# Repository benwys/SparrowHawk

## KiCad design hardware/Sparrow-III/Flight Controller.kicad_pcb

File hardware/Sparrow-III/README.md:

# Sparrow-III

Projekt KiCad: **Flight Controller.kicad_pro**.

- [Dokumentacja i stan prac](../../docs/Sparrow-III/README.md)
- [Backlog](../../docs/Sparrow-III/BACKLOG.md)
- [Raport kontroli](../../docs/Sparrow-III/REVIEW.md)
- [Skrypty](../../tools/Sparrow-III/README.md)

Biblioteki są lokalne w `Libraries/`; tabele używają `${KIPRJMOD}`.
Etap: placement, przed pełnym routingiem.

[Wspólna próba trasowania](attempts/placement-closure-20260912/Flight%20Controller.kicad_pro) jest osobnym projektem z miedzią. Główny placement pozostaje bez routingu.

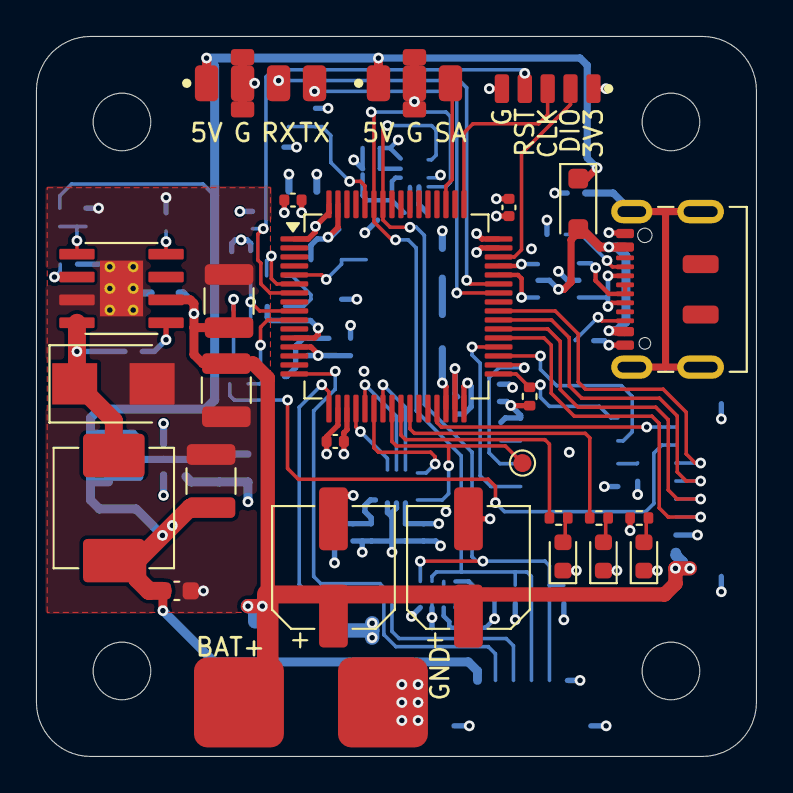
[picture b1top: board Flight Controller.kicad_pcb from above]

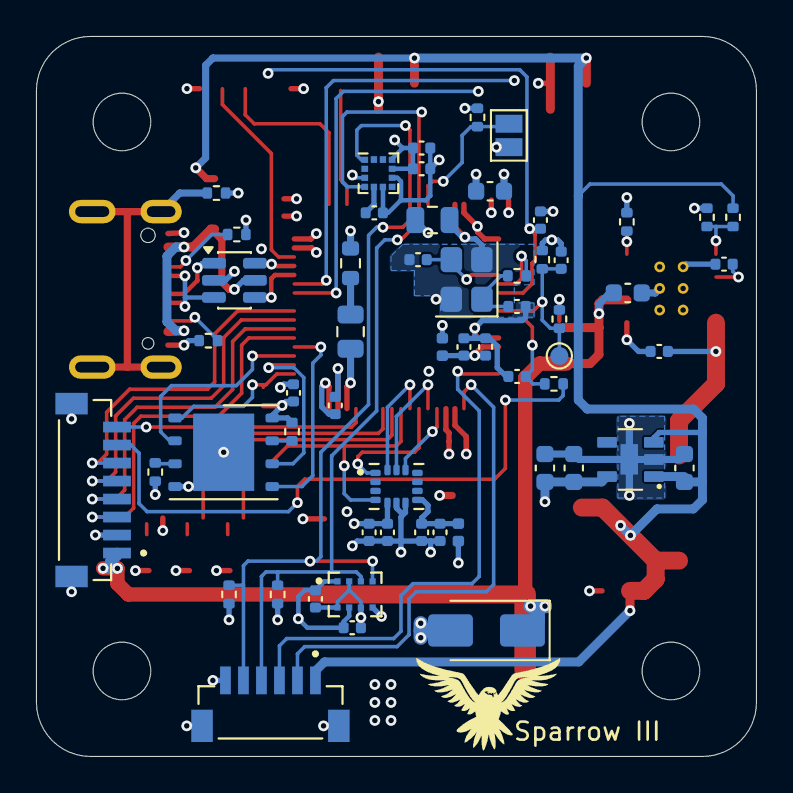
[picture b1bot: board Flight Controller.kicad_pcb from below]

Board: 4 copper layers, 40.0 x 40.0 mm, 89 parts (58 on the bottom side), 60 nets.

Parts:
C_3V3_BULK1, C_5V_BULK1: 10uF; C_0603_1608Metric
C_B1, C_B5: 47uF; CP_Elec_6.3x5.8
C_BARO1, C_BARO2: 100nF; C_0402_1005Metric
C_BUCK_BOOT1: 100nF; C_0402_1005Metric
C_BUCK_IN1, C_BUCK_IN2: 4.7uF; C_1210_3225Metric
C_BUCK_IN3: 100nF; C_0603_1608Metric
C_BUCK_OUT1: 100uF; C_1210_3225Metric
C_BUCK_SS1: 22nF; C_0402_1005Metric
C_CURR_F1: 1uF; C_0402_1005Metric
C_FLASH1: 100nF; C_0402_1005Metric
C_HSE1, C_HSE2: 12pF; C_0402_1005Metric
C_IMU_VDD1: 2.2uF; C_0402_1005Metric
C_IMU_VDD2: 100nF; C_0402_1005Metric
C_IMU_VIO1: 100nF; C_0402_1005Metric
C_IMU_VIO2: 10nF; C_0402_1005Metric
C_LDO_IN1: 2.2uF; C_0603_1608Metric
C_LDO_OUT1: 2.2uF; C_0603_1608Metric
C_MAG_BULK1: 22uF; C_0805_2012Metric
C_MAG_SET1: 220nF; C_0402_1005Metric
C_MAG_VDD1: 100nF; C_0402_1005Metric
C_MAG_VIO1: 100nF; C_0402_1005Metric
C_NRST1: 100nF; C_0402_1005Metric
C_VBAT_ADC1: 100nF; C_0402_1005Metric
C_VCAP1: 4.7uF; C_0805_2012Metric
C_VDD1, C_VDD2, C_VDD3, C_VDD4: 100nF; C_0402_1005Metric
C_VDDA1: 1uF; C_0402_1005Metric
C_VDDA_HF1: 100nF; C_0402_1005Metric
C_VDD_BULK1: 4.7uF; C_0603_1608Metric
D_BUCK1: STPS3H100U; D_SMB
D_TVS1: SMAJ26A; D_SMA
D_USB_VBUS1: PMEG2010AEH; D_SOD-123F
FB_IMU1: 600R @ 100MHz; L_0402_1005Metric
FB_VDDA1: 100R @ 100MHz; L_0402_1005Metric
H_MNT1, H_MNT2, H_MNT3, H_MNT4: MountingHole 3.2mm_M3; MountingHole_3.2mm_M3
JP_BOOT0: Jumper2; SolderJumper-2_P1.3mm_Open_Pad1.0x1.5mm
J_BAT1: Conn_01x02; VBAT_SolderPad_2x_5x5mm
J_ESC1: BM08B-SRSS-TB_LF__SN_; JST_BM08B-SRSS-TB_LF__SN_
J_GPS1: BM06B-SRSS-TB_LF__SN_; JST_BM06B-SRSS-TB_LF__SN_
J_RX1: RX Pads; SolderPads_RX_1x04
J_SWD1: SWD Pads; SolderPads_SWD_1x05
J_USB1: DX07S016JA1R1500; USB_C_Receptacle_JAE_DX07S016JA1R1500
J_VTX2: VTX: 5V / GND / SA; SolderPads_VTX_1x03
LED_PWR1: LED Green 0603; LED_0603_1608Metric
LED_STAT1: LED Blue 0603; LED_0603_1608Metric
LED_STAT2: LED Red 0603; LED_0603_1608Metric
LOGO1: Sparrowhawk_Logo
L_BUCK1: 6.8uH; L_Vishay_IHLP-2525CZ-01
R_BOOT0: 10k; R_0402_1005Metric
R_BUCK_FB1: 100k; R_0402_1005Metric
R_BUCK_FB2: 17.8k; R_0402_1005Metric
R_BUCK_RT1: 49.9k; R_0402_1005Metric
R_CC1, R_CC2: 5.1k; R_0402_1005Metric
R_CURR_F1: 1k; R_0402_1005Metric
R_FLASH_CS1: 10k; R_0402_1005Metric
R_FLASH_HD1: 10k; R_0402_1005Metric
R_FLASH_WP1: 10k; R_0402_1005Metric
R_HSE2: 0R; R_0402_1005Metric
R_I2C_SCL1, R_I2C_SDA1: 4.7k; R_0402_1005Metric
R_LED1, R_LED2, R_LED3: 1k; R_0402_1005Metric
R_USB_SH1: 0R; R_0402_1005Metric
R_VBAT_D1: 100k; R_0402_1005Metric
R_VBAT_D2: 10k; R_0402_1005Metric
R_VCAP_ESR1: 0.15R; R_0603_1608Metric
TP_IMU_INT_0: Test Point; TestPoint_Pad_D1.0mm
TP_VBAT_ADC_0: Test Point; TestPoint_Pad_D1.0mm
U_BARO1: DPS368; XDCR_DPS310
U_BUCK1: LMR14030SDDAR; SOIC127P600X170-9N_SparrowIII
U_ESD1: USBLC6-2SC6; SOT-23-6
U_FLASH1: W25Q128JVPIQ; WSON-8-1EP_6x5mm_P1.27mm_EP3.4x4.3mm
U_IMU1: ICM-42688-P; PQFN50P300X250X97-14N
U_LDO1: TLV75533PDYDR; SOT-23-5_ThermalPad_TI_DYD0005A
U_MAG1: LIS2MDLTR; LGA-12_2x2mm_P0.5mm
U_MCU1: STM32F722RETx; LQFP-64_10x10mm_P0.5mm
Y_HSE1: 8MHz; Crystal_SMD_3225-4Pin_3.2x2.5mm

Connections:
+3V3: C_3V3_BULK1.1, C_BARO1.1, C_BARO2.1, C_FLASH1.1, C_IMU_VIO1.1, C_IMU_VIO2.1, C_LDO_OUT1.1, C_MAG_BULK1.1, C_MAG_VDD1.1, C_MAG_VIO1.1, C_VDD1.1, C_VDD2.1, C_VDD3.1, C_VDD4.1, C_VDD_BULK1.1, FB_IMU1.2, FB_VDDA1.1, JP_BOOT0.1 (A), J_SWD1.1, R_FLASH_CS1.1, R_FLASH_HD1.1, R_FLASH_WP1.1, R_I2C_SCL1.1, R_I2C_SDA1.2, R_LED1.1, U_BARO1.2 (~CSB), U_BARO1.6 (VDDIO), U_BARO1.8 (VDD), U_FLASH1.8 (VCC), U_IMU1.5 (VDDIO), U_LDO1.5 (VOUT), U_MAG1.3 (~CS), U_MAG1.9 (Vdd), U_MAG1.10 (Vdd_IO), U_MCU1.1 (VBAT), U_MCU1.19 (VDD), U_MCU1.32 (VDD), U_MCU1.48 (VDD), U_MCU1.64 (VDD)
+5V: C_5V_BULK1.1, C_BUCK_OUT1.1, C_LDO_IN1.1, D_USB_VBUS1.1 (K), J_GPS1.1, J_RX1.1, J_VTX2.1, L_BUCK1.2, R_BUCK_FB1.1, U_LDO1.1 (VIN), U_LDO1.3 (EN)
/Interfaces&IO/+5V_USB: D_USB_VBUS1.2 (A), J_USB1.A4 (VBUS), J_USB1.A9 (VBUS), J_USB1.B4 (VBUS), J_USB1.B9 (VBUS), U_ESD1.5 (VBUS)
/Interfaces&IO/ESC_CURR: C_CURR_F1.1, R_CURR_F1.1, U_MCU1.10 (PC2)
/Interfaces&IO/ESC_CURR_IN: J_ESC1.7, R_CURR_F1.2
/Interfaces&IO/ESC_TEL: J_ESC1.8, U_MCU1.29 (PB11)
/Interfaces&IO/GPS_RX: J_GPS1.2, U_MCU1.17 (PA3)
/Interfaces&IO/GPS_TX: J_GPS1.3, U_MCU1.16 (PA2)
/Interfaces&IO/M1: J_ESC1.3, U_MCU1.37 (PC6)
/Interfaces&IO/M2: J_ESC1.4, U_MCU1.38 (PC7)
/Interfaces&IO/M3: J_ESC1.5, U_MCU1.39 (PC8)
/Interfaces&IO/M4: J_ESC1.6, U_MCU1.40 (PC9)
/Interfaces&IO/RC_RX: J_RX1.3, U_MCU1.43 (PA10)
/Interfaces&IO/RC_TX: J_RX1.4, U_MCU1.42 (PA9)
/Interfaces&IO/USB_C_DN: J_USB1.A7 (D-), J_USB1.B7 (D-), U_ESD1.3 (I/O2)
/Interfaces&IO/USB_C_DP: J_USB1.A6 (D+), J_USB1.B6 (D+), U_ESD1.1 (I/O1)
/Interfaces&IO/USB_DN: U_ESD1.4 (I/O2), U_MCU1.44 (PA11)
/Interfaces&IO/USB_DP: U_ESD1.6 (I/O1), U_MCU1.45 (PA12)
/Interfaces&IO/VTX_TX: J_VTX2.3, U_MCU1.51 (PC10)
/MCU Core/FLASH_CS: R_FLASH_CS1.2, U_FLASH1.1 (~CS), U_MCU1.33 (PB12)
/MCU Core/I2C1_SCL: J_GPS1.5, R_I2C_SCL1.2, U_BARO1.4 (SCK), U_MAG1.1 (SCL/SPC), U_MCU1.58 (PB6)
/MCU Core/I2C1_SDA: J_GPS1.4, R_I2C_SDA1.1, U_BARO1.3 (SDI), U_MAG1.4 (SDA/SDI/SDO), U_MCU1.59 (PB7)
/MCU Core/IMU_CS: U_IMU1.12 (AP_CS), U_MCU1.20 (PA4)
/MCU Core/IMU_INT: TP_IMU_INT_0.1 (1_1), U_IMU1.4 (INT1/INT), U_MCU1.24 (PC4)
/MCU Core/LED_STAT1: R_LED2.1, U_MCU1.25 (PB0)
/MCU Core/LED_STAT2: R_LED3.1, U_MCU1.26 (PB1)
/MCU Core/NRST: C_NRST1.1, J_SWD1.4, U_MCU1.7 (NRST)
/MCU Core/RCC_OSC_IN: C_HSE2.2, U_MCU1.5 (PH0), Y_HSE1.3
/MCU Core/RCC_OSC_OUT: R_HSE2.2, U_MCU1.6 (PH1)
/MCU Core/SPI1_MISO: U_IMU1.1 (AP_SDO/AP_AD0), U_MCU1.22 (PA6)
/MCU Core/SPI1_MOSI: U_IMU1.14 (AP_SDA/AP_SDIO/AP_SDI), U_MCU1.23 (PA7)
/MCU Core/SPI1_SCK: U_IMU1.13 (AP_SCL/AP_SCLK), U_MCU1.21 (PA5)
/MCU Core/SPI2_MISO: U_FLASH1.2 (DO/IO_{1}), U_MCU1.35 (PB14)
/MCU Core/SPI2_MOSI: U_FLASH1.5 (DI/IO_{0}), U_MCU1.36 (PB15)
/MCU Core/SPI2_SCK: U_FLASH1.6 (CLK), U_MCU1.34 (PB13)
/MCU Core/SWCLK: J_SWD1.3, U_MCU1.49 (PA14)
/MCU Core/SWDIO: J_SWD1.2, U_MCU1.46 (PA13)
/MCU Core/VBAT_ADC: C_VBAT_ADC1.1, R_VBAT_D1.1, R_VBAT_D2.2, TP_VBAT_ADC_0.1 (1_1), U_MCU1.9 (PC1)
/MCU Core/VCAP_RETURN: C_VCAP1.2, R_VCAP_ESR1.1
/Sensors/MAG_C1: C_MAG_SET1.1, U_MAG1.5 (C1)
GND: C_3V3_BULK1.2, C_5V_BULK1.2, C_B1.2, C_B5.2, C_BARO1.2, C_BARO2.2, C_BUCK_IN1.2, C_BUCK_IN2.2, C_BUCK_IN3.2, C_BUCK_OUT1.2, C_BUCK_SS1.2, C_CURR_F1.2, C_FLASH1.2, C_HSE1.1, C_HSE2.1, C_IMU_VDD1.2, C_IMU_VDD2.2, C_IMU_VIO1.2, C_IMU_VIO2.2, C_LDO_IN1.2, C_LDO_OUT1.2, C_MAG_BULK1.2, C_MAG_SET1.2, C_MAG_VDD1.2, C_MAG_VIO1.2, C_NRST1.2, C_VBAT_ADC1.2, C_VDD1.2, C_VDD2.2, C_VDD3.2, C_VDD4.2, C_VDDA1.2, C_VDDA_HF1.2, C_VDD_BULK1.2, D_BUCK1.2 (A), D_TVS1.2 (A2), J_BAT1.2, J_ESC1.2, J_ESC1.S1 (SHIELD), J_ESC1.S2 (SHIELD), J_GPS1.6, J_GPS1.S1 (SHIELD), J_GPS1.S2 (SHIELD), J_RX1.2, J_RX1.S1 (SHIELD), J_RX1.S2 (SHIELD), J_SWD1.5, J_USB1.A1 (GND), J_USB1.A12 (GND), J_USB1.B1 (GND), J_USB1.B12 (GND), J_VTX2.2, LED_PWR1.1 (K), LED_STAT1.1 (K), LED_STAT2.1 (K), R_BOOT0.1, R_BUCK_FB2.2, R_BUCK_RT1.2, R_CC1.2, R_CC2.2, R_USB_SH1.2, R_VBAT_D2.1, R_VCAP_ESR1.2, U_BARO1.1 (GND), U_BARO1.5 (SDO), U_BARO1.7 (GND), U_BUCK1.7 (GND), U_BUCK1.9 (GND), U_BUCK1.V1 (GND), U_BUCK1.V2 (GND), U_BUCK1.V3 (GND), U_BUCK1.V4 (GND), U_BUCK1.V5 (GND), U_BUCK1.V6 (GND), U_ESD1.2 (GND), U_FLASH1.4 (GND), U_FLASH1.9 (EP), U_IMU1.6 (GND), U_IMU1.7 (RESV_7), U_LDO1.2 (GND), U_LDO1.6 (EP), U_MAG1.6 (GND), U_MAG1.8 (GND), U_MCU1.12 (VSSA), U_MCU1.18 (VSS), U_MCU1.31 (VSS), U_MCU1.47 (VSS), U_MCU1.63 (VSS), Y_HSE1.2 (G), Y_HSE1.4 (G)
unnamed: C_HSE1.2, R_HSE2.1, Y_HSE1.1
unnamed: C_BUCK_BOOT1.2, D_BUCK1.1 (K), L_BUCK1.1, U_BUCK1.8 (SW)
unnamed: JP_BOOT0.2 (B), R_BOOT0.2, U_MCU1.60 (BOOT0)
unnamed: J_USB1.A5 (CC1), R_CC1.1
unnamed: J_USB1.B5 (CC2), R_CC2.1
unnamed: J_USB1.SH (SHIELD), R_USB_SH1.1
unnamed: LED_PWR1.2 (A), R_LED1.2
unnamed: LED_STAT1.2 (A), R_LED2.2
unnamed: LED_STAT2.2 (A), R_LED3.2
unnamed: C_BUCK_BOOT1.1, U_BUCK1.1 (BOOT)
unnamed: R_BUCK_FB1.2, R_BUCK_FB2.1, U_BUCK1.5 (FB)
unnamed: R_BUCK_RT1.1, U_BUCK1.4 (RT/SYNC)
unnamed: C_BUCK_SS1.1, U_BUCK1.6 (SS)
unnamed: R_FLASH_HD1.2, U_FLASH1.7 (~HOLD/~RESET/IO_{3})
unnamed: R_FLASH_WP1.2, U_FLASH1.3 (~WP/IO_{2})
unnamed: C_IMU_VDD1.1, C_IMU_VDD2.1, FB_IMU1.1, U_IMU1.8 (VDD)
unnamed: C_VCAP1.1, U_MCU1.30 (VCAP_1)
unnamed: C_VDDA1.1, C_VDDA_HF1.1, FB_VDDA1.2, U_MCU1.13 (VDDA)
VBAT: C_B1.1, C_B5.1, C_BUCK_IN1.1, C_BUCK_IN2.1, C_BUCK_IN3.1, D_TVS1.1 (A1), J_BAT1.1, J_ESC1.1, R_VBAT_D1.2, U_BUCK1.2 (VIN)

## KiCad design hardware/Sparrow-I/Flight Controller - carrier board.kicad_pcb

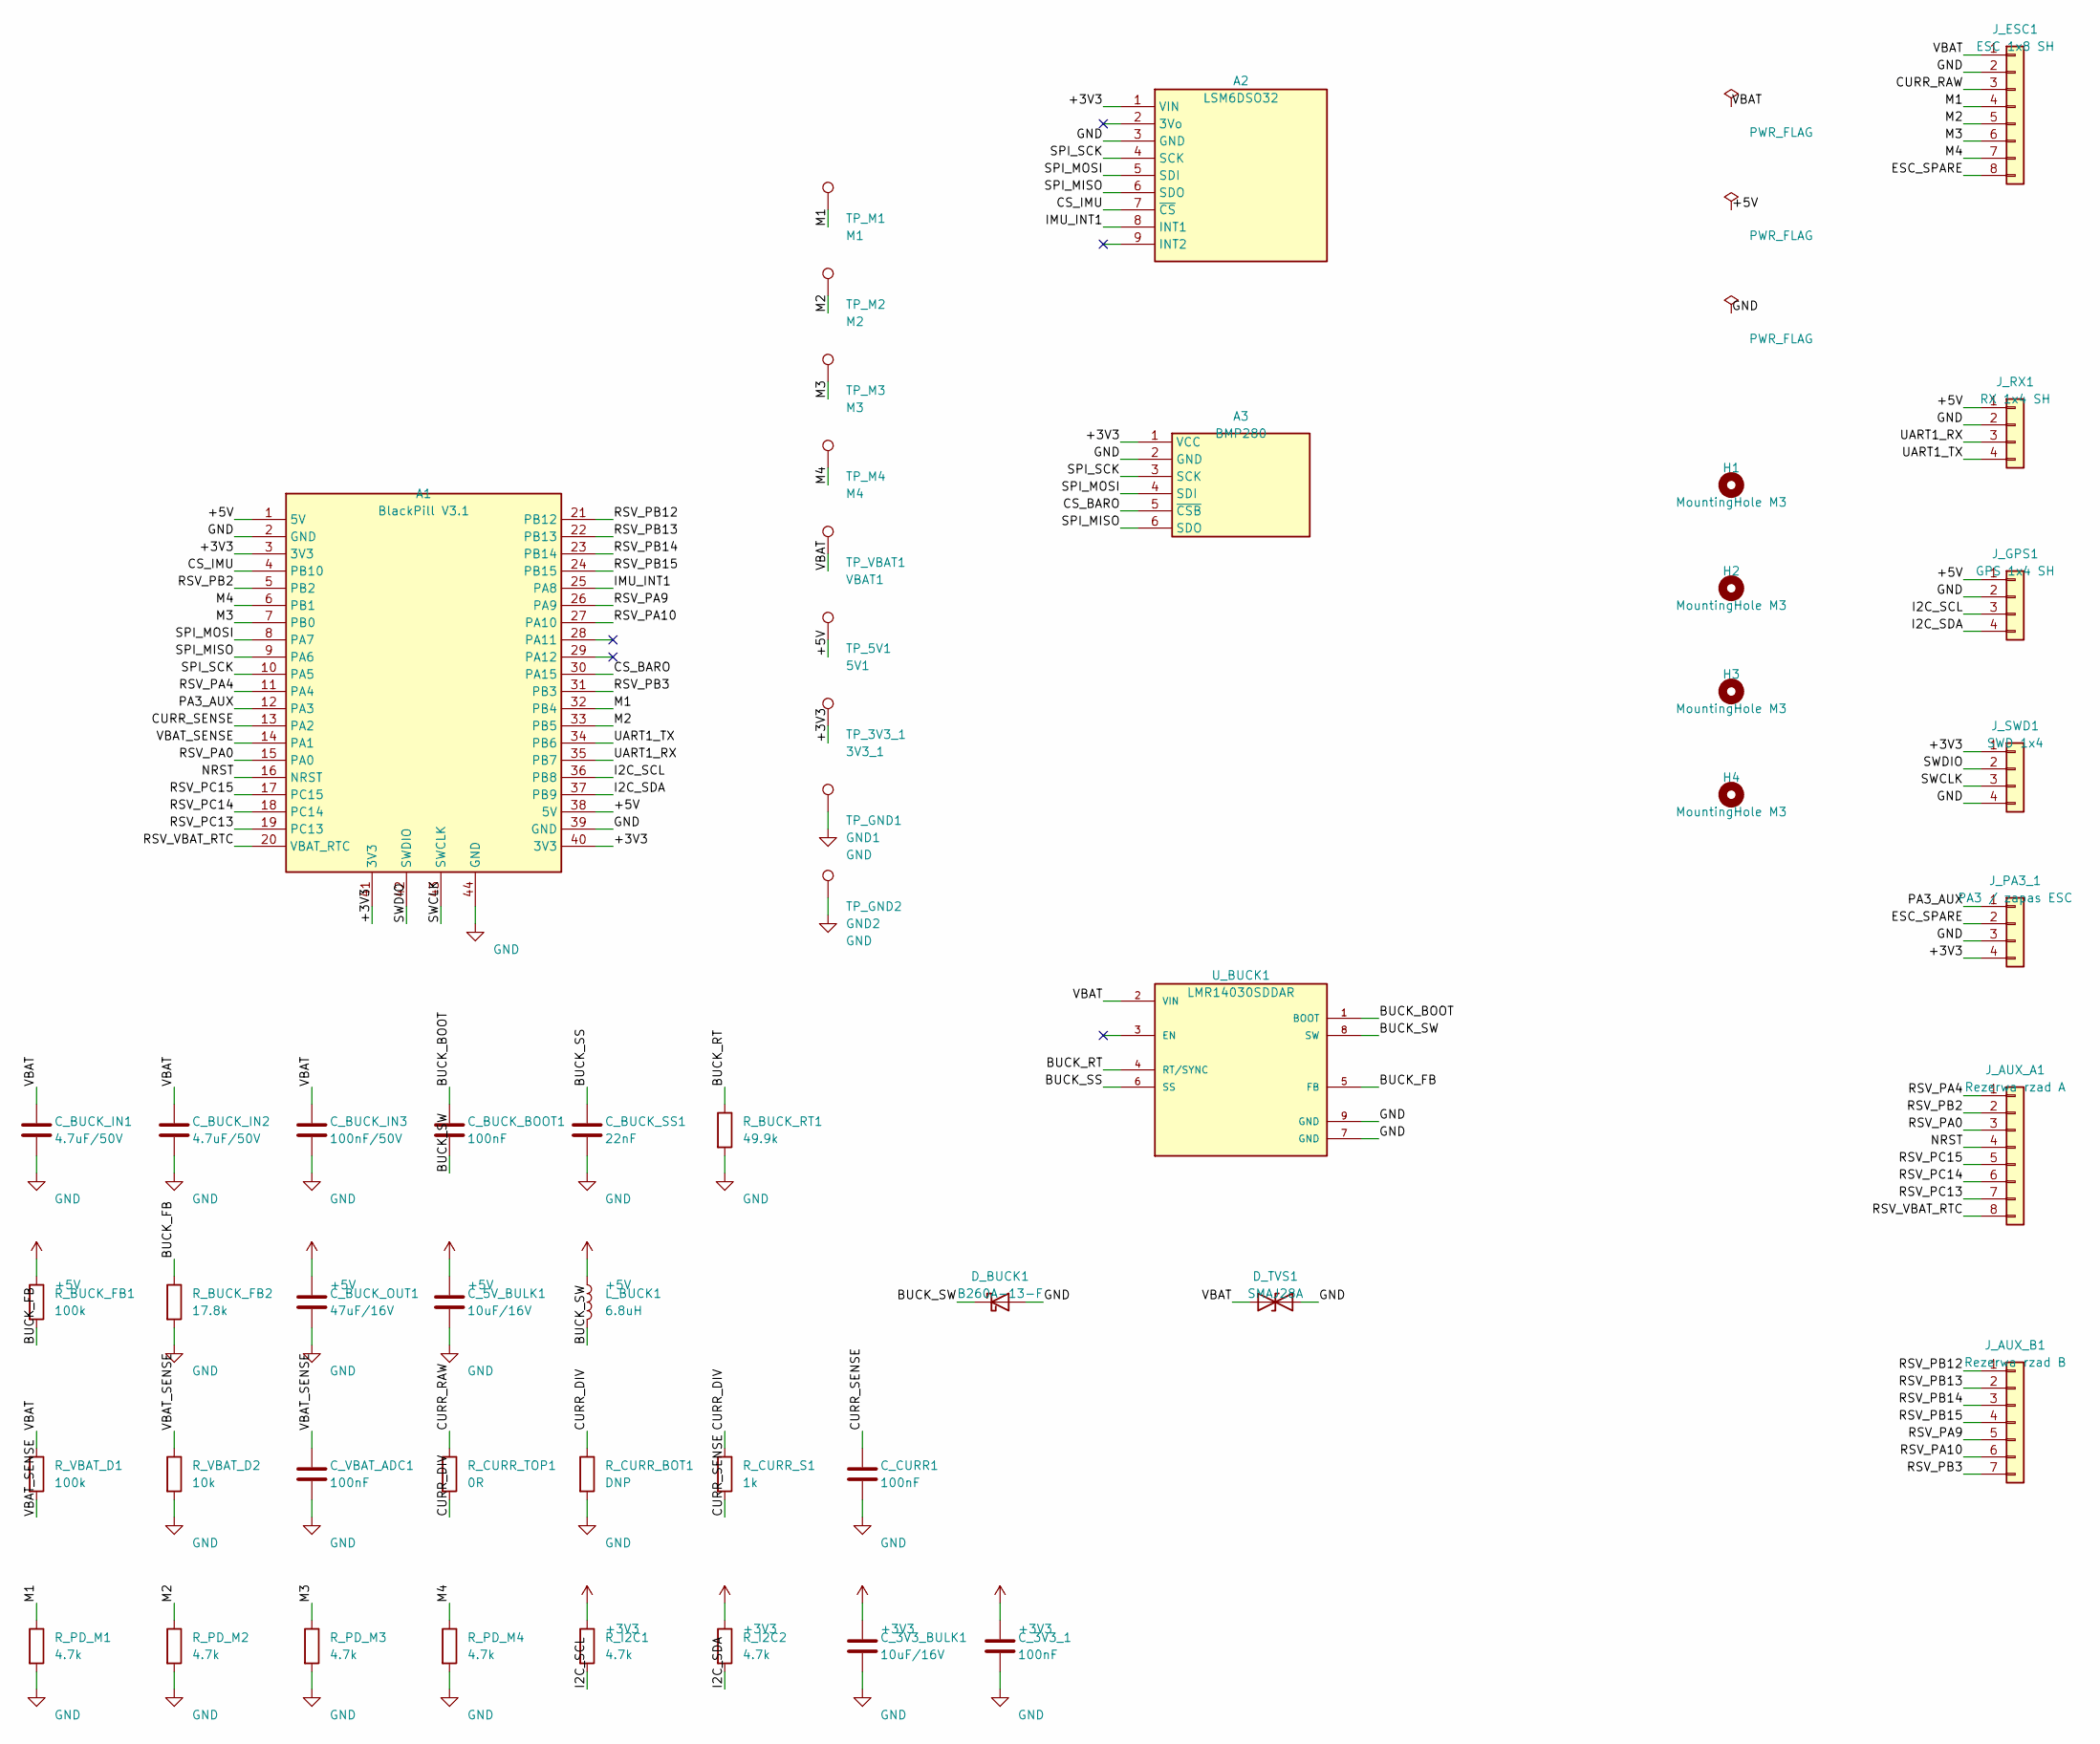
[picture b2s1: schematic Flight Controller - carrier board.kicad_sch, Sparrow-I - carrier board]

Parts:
A1: BlackPill V3.1; Module_BlackPill_STM32F411_WeAct_V31
A2: LSM6DSO32; Module_LSM6DSO32_Adafruit_4692
A3: BMP280; Module_BMP280_6pin
C_3V3_1: 100nF; C_0402_1005Metric
C_3V3_BULK1, C_5V_BULK1: 10uF/16V; C_0805_2012Metric
C_BUCK_BOOT1: 100nF; C_0402_1005Metric
C_BUCK_IN1, C_BUCK_IN2: 4.7uF/50V; C_1210_3225Metric
C_BUCK_IN3: 100nF/50V; C_0402_1005Metric
C_BUCK_OUT1: 47uF/16V; C_1210_3225Metric
C_BUCK_SS1: 22nF; C_0402_1005Metric
C_CURR1: 100nF; C_0402_1005Metric
C_VBAT_ADC1: 100nF; C_0402_1005Metric
D_BUCK1: B260A-13-F; D_SMA
D_TVS1: SMAJ28A; D_SMA
H1, H2, H3, H4: MountingHole M3; MountingHole_3.2mm_M3
J_AUX_A1: Rezerwa rzad A; PinHeader_1x08_P2.54mm_Vertical
J_AUX_B1: Rezerwa rzad B; PinHeader_1x07_P2.54mm_Vertical
J_ESC1: ESC 1x8 SH; JST_SH_SM08B-SRSS-TB_1x08-1MP_P1.00mm_Horizontal
J_GPS1: GPS 1x4 SH; JST_SH_SM04B-SRSS-TB_1x04-1MP_P1.00mm_Horizontal
J_PA3_1: PA3 / zapas ESC; PinHeader_1x04_P2.54mm_Vertical
J_RX1: RX 1x4 SH; JST_SH_SM04B-SRSS-TB_1x04-1MP_P1.00mm_Horizontal
J_SWD1: SWD 1x4; PinHeader_1x04_P2.54mm_Vertical
L_BUCK1: 6.8uH; L_Sunlord_SWPA6028S
R_BUCK_FB1: 100k; R_0402_1005Metric
R_BUCK_FB2: 17.8k; R_0402_1005Metric
R_BUCK_RT1: 49.9k; R_0402_1005Metric
R_CURR_BOT1: DNP; R_0402_1005Metric
R_CURR_S1: 1k; R_0402_1005Metric
R_CURR_TOP1: 0R; R_0402_1005Metric
R_I2C1, R_I2C2: 4.7k; R_0402_1005Metric
R_PD_M1, R_PD_M2, R_PD_M3, R_PD_M4: 4.7k; R_0402_1005Metric
R_VBAT_D1: 100k; R_0402_1005Metric
R_VBAT_D2: 10k; R_0402_1005Metric
TP_3V3_1: 3V3_1; TestPoint_Pad_D1.5mm
TP_5V1: 5V1; TestPoint_Pad_D1.5mm
TP_GND1: GND1; TestPoint_Pad_D1.5mm
TP_GND2: GND2; TestPoint_Pad_D1.5mm
TP_M1: M1; TestPoint_Pad_D1.5mm
TP_M2: M2; TestPoint_Pad_D1.5mm
TP_M3: M3; TestPoint_Pad_D1.5mm
TP_M4: M4; TestPoint_Pad_D1.5mm
TP_VBAT1: VBAT1; TestPoint_Pad_D1.5mm
U_BUCK1: LMR14030SDDAR; SOIC127P600X170-9N

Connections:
+3V3: A1.3 (3V3), A1.40 (3V3), A1.41 (3V3), A2.1 (VIN), A3.1 (VCC), C_3V3_1.1, C_3V3_BULK1.1, J_PA3_1.4, J_SWD1.1, R_I2C1.1, R_I2C2.1, TP_3V3_1.1 (1_1)
+5V: A1.1 (5V), A1.38 (5V), C_5V_BULK1.1, C_BUCK_OUT1.1, J_GPS1.1, J_RX1.1, L_BUCK1.1, R_BUCK_FB1.1, TP_5V1.1 (1_1)
/BUCK_BOOT: C_BUCK_BOOT1.1, U_BUCK1.1 (BOOT)
/BUCK_FB: R_BUCK_FB1.2, R_BUCK_FB2.1, U_BUCK1.5 (FB)
/BUCK_RT: R_BUCK_RT1.1, U_BUCK1.4 (RT/SYNC)
/BUCK_SS: C_BUCK_SS1.1, U_BUCK1.6 (SS)
/BUCK_SW: C_BUCK_BOOT1.2, D_BUCK1.1 (K), L_BUCK1.2, U_BUCK1.8 (SW)
/CS_BARO: A1.30 (PA15), A3.5 (~CSB)
/CS_IMU: A1.4 (PB10), A2.7 (~CS)
/CURR_DIV: R_CURR_BOT1.1, R_CURR_S1.1, R_CURR_TOP1.2
/CURR_RAW: J_ESC1.3, R_CURR_TOP1.1
/CURR_SENSE: A1.13 (PA2), C_CURR1.1, R_CURR_S1.2
/ESC_SPARE: J_ESC1.8, J_PA3_1.2
/I2C_SCL: A1.36 (PB8), J_GPS1.3, R_I2C1.2
/I2C_SDA: A1.37 (PB9), J_GPS1.4, R_I2C2.2
/IMU_INT1: A1.25 (PA8), A2.8 (INT1)
/M1: A1.32 (PB4), J_ESC1.4, R_PD_M1.1, TP_M1.1 (1_1)
/M2: A1.33 (PB5), J_ESC1.5, R_PD_M2.1, TP_M2.1 (1_1)
/M3: A1.7 (PB0), J_ESC1.6, R_PD_M3.1, TP_M3.1 (1_1)
/M4: A1.6 (PB1), J_ESC1.7, R_PD_M4.1, TP_M4.1 (1_1)
/NRST: A1.16 (NRST), J_AUX_A1.4
/PA3_AUX: A1.12 (PA3), J_PA3_1.1
/RSV_PA0: A1.15 (PA0), J_AUX_A1.3
/RSV_PA4: A1.11 (PA4), J_AUX_A1.1
/RSV_PA9: A1.26 (PA9), J_AUX_B1.5
/RSV_PA10: A1.27 (PA10), J_AUX_B1.6
/RSV_PB2: A1.5 (PB2), J_AUX_A1.2
/RSV_PB3: A1.31 (PB3), J_AUX_B1.7
/RSV_PB12: A1.21 (PB12), J_AUX_B1.1
/RSV_PB13: A1.22 (PB13), J_AUX_B1.2
/RSV_PB14: A1.23 (PB14), J_AUX_B1.3
/RSV_PB15: A1.24 (PB15), J_AUX_B1.4
/RSV_PC13: A1.19 (PC13), J_AUX_A1.7
/RSV_PC14: A1.18 (PC14), J_AUX_A1.6
/RSV_PC15: A1.17 (PC15), J_AUX_A1.5
/RSV_VBAT_RTC: A1.20 (VBAT_RTC), J_AUX_A1.8
/SPI_MISO: A1.9 (PA6), A2.6 (SDO), A3.6 (SDO)
/SPI_MOSI: A1.8 (PA7), A2.5 (SDI), A3.4 (SDI)
/SPI_SCK: A1.10 (PA5), A2.4 (SCK), A3.3 (SCK)
/SWCLK: A1.43 (SWCLK), J_SWD1.3
/SWDIO: A1.42 (SWDIO), J_SWD1.2
/UART1_RX: A1.35 (PB7), J_RX1.3
/UART1_TX: A1.34 (PB6), J_RX1.4
/VBAT: C_BUCK_IN1.1, C_BUCK_IN2.1, C_BUCK_IN3.1, D_TVS1.1 (A1), J_ESC1.1, R_VBAT_D1.1, TP_VBAT1.1 (1_1), U_BUCK1.2 (VIN)
/VBAT_SENSE: A1.14 (PA1), C_VBAT_ADC1.1, R_VBAT_D1.2, R_VBAT_D2.1
GND: A1.2 (GND), A1.39 (GND), A1.44 (GND), A2.3 (GND), A3.2 (GND), C_3V3_1.2, C_3V3_BULK1.2, C_5V_BULK1.2, C_BUCK_IN1.2, C_BUCK_IN2.2, C_BUCK_IN3.2, C_BUCK_OUT1.2, C_BUCK_SS1.2, C_CURR1.2, C_VBAT_ADC1.2, D_BUCK1.2 (A), D_TVS1.2 (A2), J_ESC1.2, J_GPS1.2, J_PA3_1.3, J_RX1.2, J_SWD1.4, R_BUCK_FB2.2, R_BUCK_RT1.2, R_CURR_BOT1.2, R_PD_M1.2, R_PD_M2.2, R_PD_M3.2, R_PD_M4.2, R_VBAT_D2.2, TP_GND1.1 (1_1), TP_GND2.1 (1_1), U_BUCK1.7 (GND), U_BUCK1.9 (GND), U_BUCK1.V1 (GND), U_BUCK1.V2 (GND), U_BUCK1.V3 (GND), U_BUCK1.V4 (GND), U_BUCK1.V5 (GND), U_BUCK1.V6 (GND)

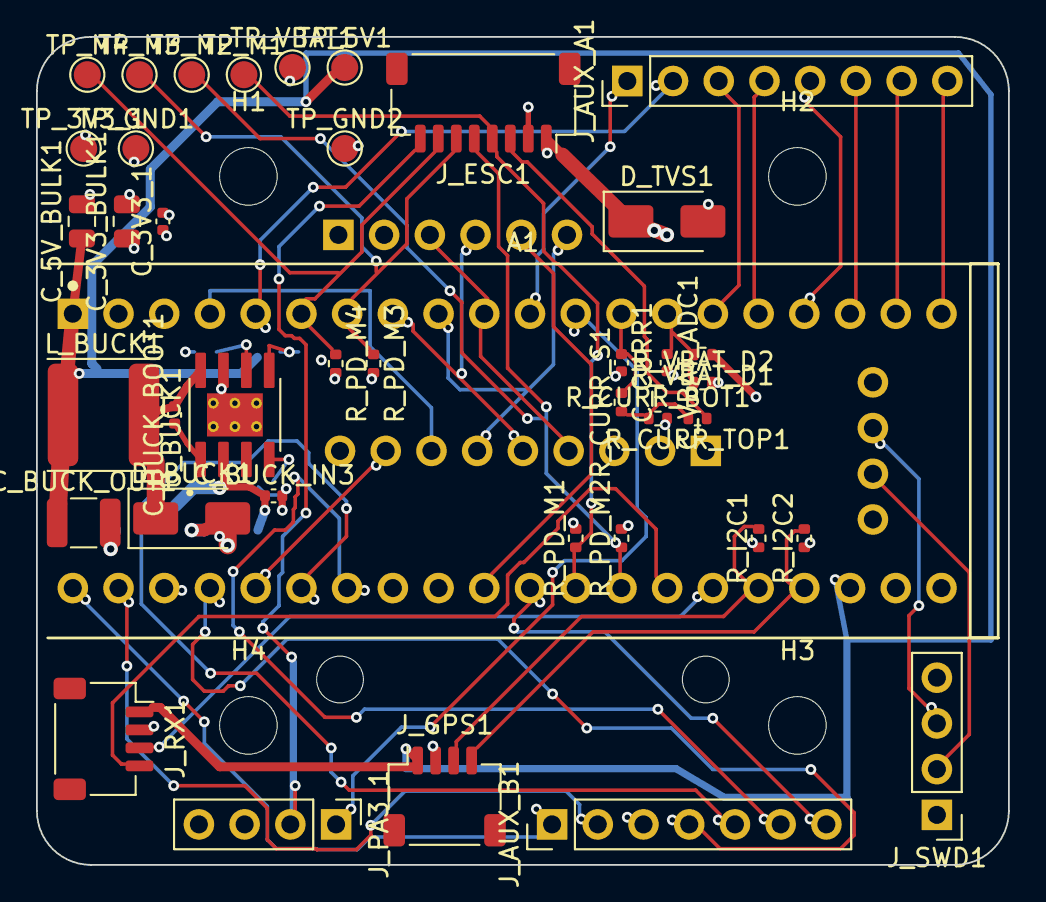
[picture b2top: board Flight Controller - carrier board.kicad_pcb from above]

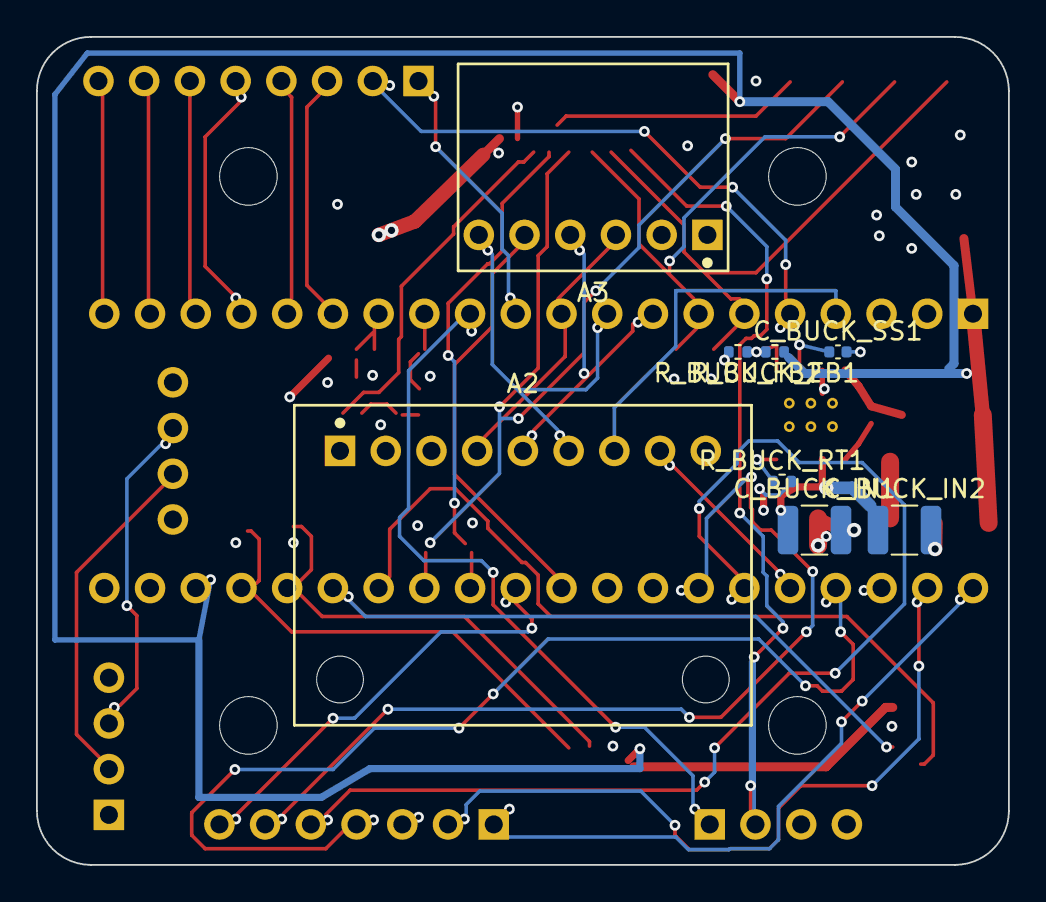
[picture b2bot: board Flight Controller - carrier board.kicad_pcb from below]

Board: 4 copper layers, 54.0 x 46.0 mm, 52 parts (8 on the bottom side), 46 nets.

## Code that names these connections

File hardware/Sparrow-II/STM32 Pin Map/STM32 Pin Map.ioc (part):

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Mcu.Name=STM32F722R(C-E)Tx
Mcu.Package=LQFP64
Mcu.UserName=STM32F722RETx
PA10.GPIOParameters=GPIO_Label
PA10.GPIO_Label=RC_RX
PA10.Mode=Asynchronous
PA10.Signal=USART1_RX
PA11.Mode=Device_Only
PA11.Signal=USB_OTG_FS_DM
PA12.Mode=Device_Only
PA12.Signal=USB_OTG_FS_DP
PA13.Mode=Serial_Wire
PA13.Signal=SYS_JTMS-SWDIO
PA14.Mode=Serial_Wire
PA14.Signal=SYS_JTCK-SWCLK
PA2.GPIOParameters=GPIO_Label
PA2.GPIO_Label=GPS_TX
PA2.Mode=Asynchronous
PA2.Signal=USART2_TX
PA3.GPIOParameters=GPIO_Label
PA3.GPIO_Label=GPS_RX
PA3.Mode=Asynchronous
PA3.Signal=USART2_RX
PA4.GPIOParameters=GPIO_Speed,PinState,GPIO_PuPd,GPIO_Label
PA4.GPIO_Label=IMU_CS
PA4.GPIO_PuPd=GPIO_NOPULL
PA4.GPIO_Speed=GPIO_SPEED_FREQ_HIGH
PA4.PinState=GPIO_PIN_SET
PA4.Signal=GPIO_Output
PA5.Mode=Full_Duplex_Master
PA5.Signal=SPI1_SCK
PA6.Mode=Full_Duplex_Master
PA6.Signal=SPI1_MISO
PA7.Mode=Full_Duplex_Master
PA7.Signal=SPI1_MOSI
PA9.GPIOParameters=GPIO_Label
PA9.GPIO_Label=RC_TX
PA9.Mode=Asynchronous
PA9.Signal=USART1_TX
PB0.GPIOParameters=GPIO_Label
PB0.GPIO_Label=LED_STAT1
PB0.Signal=GPIO_Output
PB1.GPIOParameters=GPIO_Label
PB1.GPIO_Label=LED_STAT1
PB1.Signal=GPIO_Output
PB10.GPIOParameters=GPIO_Label
PB10.GPIO_Label=ESC_TEL
PB10.Mode=Asynchronous
PB10.Signal=USART3_TX
PB11.Mode=Asynchronous
PB11.Signal=USART3_RX
PB12.GPIOParameters=GPIO_Speed,PinState,GPIO_Label
PB12.GPIO_Label=FLASH_CS
PB12.GPIO_Speed=GPIO_SPEED_FREQ_HIGH
PB12.PinState=GPIO_PIN_SET
PB12.Signal=GPIO_Output
PB13.Mode=Full_Duplex_Master
PB13.Signal=SPI2_SCK
PB14.Mode=Full_Duplex_Master
PB14.Signal=SPI2_MISO
PB15.Mode=Full_Duplex_Master
PB15.Signal=SPI2_MOSI
PB2.GPIOParameters=GPIO_Speed,PinState,GPIO_Label
PB2.GPIO_Label=OSD_CS
PB2.GPIO_Speed=GPIO_SPEED_FREQ_HIGH
PB2.PinState=GPIO_PIN_SET
PB2.Signal=GPIO_Output
PB3.Mode=Full_Duplex_Master
PB3.Signal=SPI3_SCK
PB4.Mode=Full_Duplex_Master
PB4.Signal=SPI3_MISO
PB5.Mode=Full_Duplex_Master
PB5.Signal=SPI3_MOSI
PB6.Mode=I2C
PB6.Signal=I2C1_SCL
PB7.Mode=I2C
PB7.Signal=I2C1_SDA
PC1.Signal=ADCx_IN11
PC10.Mode=Half_duplex(single_wire_mode)
PC10.Signal=UART4_TX
PC13.GPIOParameters=GPIO_Label
PC13.GPIO_Label=BUZZER_CTRL
PC13.Signal=GPIO_Output
PC2.Signal=ADCx_IN12
PC4.GPIOParameters=GPIO_Label
PC4.GPIO_Label=IMU_INT
PC4.Signal=GPXTI4
PC6.Signal=S_TIM3_CH1
PC7.Signal=S_TIM3_CH2
PC8.Signal=S_TIM3_CH3
PC9.Signal=S_TIM3_CH4
PH0-OSC_IN.Mode=HSE-External-Oscillator
PH0-OSC_IN.Signal=RCC_OSC_IN
PH1-OSC_OUT.Mode=HSE-External-Oscillator
PH1-OSC_OUT.Signal=RCC_OSC_OUT
RCC.HSE_VALUE=25000000
board=custom

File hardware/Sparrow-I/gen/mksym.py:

#!/usr/bin/env python3
"""Generuje symbole modulow dla Sparrow-I."""
import os

SYM = "/home/benio/Desktop/SparrowHawk/hardware/Sparrow-I/Libraries/Symbols"
os.makedirs(SYM, exist_ok=True)

def pin(etype, x, y, ang, name, num, length=5.08):
    return f'''\t\t\t(pin {etype} line
\t\t\t\t(at {x} {y} {ang})
\t\t\t\t(length {length})
\t\t\t\t(name "{name}" (effects (font (size 1.27 1.27))))
\t\t\t\t(number "{num}" (effects (font (size 1.27 1.27))))
\t\t\t)
'''

def prop(nm, val, x, y, hide=False, size=1.27, justify=None):
    h = "\n\t\t\t(hide yes)" if hide else ""
    j = f"\n\t\t\t\t(justify {justify})" if justify else ""
    return f'''\t\t(property "{nm}" "{val}"
\t\t\t(at {x} {y} 0){h}
\t\t\t(effects (font (size {size} {size})){j})
\t\t)
'''

def sym_head(name, ref, value, fp, ds, descr, kw, refpos, valpos):
    return f'''\t(symbol "{name}"
\t\t(pin_names (offset 0.508))
\t\t(exclude_from_sim no)
\t\t(in_bom yes)
\t\t(on_board yes)
''' + prop("Reference", ref, refpos[0], refpos[1], justify="left") \
    + prop("Value", value, valpos[0], valpos[1], size=0.9, justify="left") \
    + prop("Footprint", fp, 0, 0, hide=True) \
    + prop("Datasheet", ds, 0, 0, hide=True) \
    + prop("Description", descr, 0, 0, hide=True) \
    + prop("ki_keywords", kw, 0, 0, hide=True)

def body(name, x1, y1, x2, y2):
    return f'''\t\t(symbol "{name}_0_1"
\t\t\t(rectangle
\t\t\t\t(start {x1} {y1})
\t\t\t\t(end {x2} {y2})
\t\t\t\t(stroke (width 0.254) (type default))
\t\t\t\t(fill (type background))
\t\t\t)
\t\t)
'''

out = ['(kicad_symbol_lib\n\t(version 20241209)\n\t(generator "sparrowhawk-mksym")\n\t(generator_version "10.0")\n']

# ------------------------------------------------------------- BlackPill
N = "Module_BlackPill_STM32F411_WeAct_V31"
ROW_A = [("5V","power_in"),("GND","power_in"),("3V3","power_out"),("PB10","bidirectional"),
         ("PB2","bidirectional"),("PB1","bidirectional"),("PB0","bidirectional"),("PA7","bidirectional"),
         ("PA6","bidirectional"),("PA5","bidirectional"),("PA4","bidirectional"),("PA3","bidirectional"),
         ("PA2","bidirectional"),("PA1","bidirectional"),("PA0","bidirectional"),("NRST","bidirectional"),
         ("PC15","bidirectional"),("PC14","bidirectional"),("PC13","bidirectional"),("VBAT_RTC","passive")]
ROW_B = [("PB12","bidirectional"),("PB13","bidirectional"),("PB14","bidirectional"),("PB15","bidirectional"),
         ("PA8","bidirectional"),("PA9","bidirectional"),("PA10","bidirectional"),("PA11","bidirectional"),
         ("PA12","bidirectional"),("PA15","bidirectional"),("PB3","bidirectional"),("PB4","bidirectional"),
         ("PB5","bidirectional"),("PB6","bidirectional"),("PB7","bidirectional"),("PB8","bidirectional"),
         ("PB9","bidirectional"),("5V","power_in"),("GND","power_in"),("3V3","passive")]
SWD = [("3V3","passive"),("SWDIO","bidirectional"),("SWCLK","input"),("GND","power_in")]

s = sym_head(N, "A", N, f"SparrowHawk_Modules:{N}",
             "https://github.com/WeActStudio/WeActStudio.MiniSTM32F4x1",
             "WeAct BlackPill V3.1 - modul STM32F411CEU6, HSE 25 MHz, gniazda 2x1x20 + SWD 1x4",
             "module blackpill stm32f411 weact", (-20.32, 31.75), (-20.32, -31.75))
s += body(N, -20.32, 27.94, 20.32, -27.94)
s += f'\t\t(symbol "{N}_1_1"\n'
for i, (nm, et) in enumerate(ROW_A):
    s += pin(et, -25.4, round(24.13 - i*2.54, 2), 0, nm, i+1)
for i, (nm, et) in enumerate(ROW_B):
    s += pin(et, 25.4, round(24.13 - i*2.54, 2), 180, nm, i+21)
for i, (nm, et) in enumerate(SWD):
    s += pin(et, -7.62 + i*5.08, -33.02, 90, nm, i+41)
s += "\t\t)\n\t)\n"
out.append(s)

# ------------------------------------------------------------- LSM6DSO32
N = "Module_LSM6DSO32_Adafruit_4692"
IMU = [("VIN","power_in"),("3Vo","power_out"),("GND","power_in"),("SCK","input"),
       ("SDI","input"),("SDO","tri_state"),("~{CS}","input"),("INT1","output"),("INT2","output")]
s = sym_head(N, "A", N, f"SparrowHawk_Modules:{N}", "https://www.adafruit.com/product/4692",
             "Adafruit LSM6DSO32 6DoF IMU breakout. SCK/SDI przez translator BSS138 + 10k "
             "(zegar praktycznie do ~2 MHz). SDO/INT1/INT2 wprost z czujnika. Zasilac VIN z 3V3.",
             "module imu lsm6dso32 adafruit spi", (-12.7, 15.24), (-12.7, -16.51))
s += body(N, -12.7, 12.7, 12.7, -12.7)
s += f'\t\t(symbol "{N}_1_1"\n'
for i, (nm, et) in enumerate(IMU):
    s += pin(et, -17.78, round(10.16 - i*2.54, 2), 0, nm, i+1)
s += "\t\t)\n\t)\n"
out.append(s)

# ------------------------------------------------------------- BMP280
N = "Module_BMP280_6pin"
BARO = [("VCC","power_in"),("GND","power_in"),("SCK","input"),
        ("SDI","input"),("~{CSB}","input"),("SDO","tri_state")]
s = sym_head(N, "A", N, f"SparrowHawk_Modules:{N}", "",
             "Modul BMP280 6-pin (GY-BMP280-3.3) na SPI. CSB nisko = SPI, SDO = MISO.",
             "module baro bmp280 spi", (-10.16, 10.16), (-10.16, -11.43))
s += body(N, -10.16, 7.62, 10.16, -7.62)
s += f'\t\t(symbol "{N}_1_1"\n'
for i, (nm, et) in enumerate(BARO):
    s += pin(et, -15.24, round(6.35 - i*2.54, 2), 0, nm, i+1)
s += "\t\t)\n\t)\n"
out.append(s)

out.append(")\n")
open(f"{SYM}/SparrowHawk_Modules.kicad_sym", "w").write("".join(out))
print("zapisane:", f"{SYM}/SparrowHawk_Modules.kicad_sym")

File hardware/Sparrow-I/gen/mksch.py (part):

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  nets={
    "1": "+5V", "2": "GND", "3": "+3V3", "4": "CS_IMU", "5": "RSV_PB2",
    "6": "M4", "7": "M3", "8": "SPI_MOSI", "9": "SPI_MISO", "10": "SPI_SCK",
    "11": "RSV_PA4", "12": "PA3_AUX", "13": "CURR_SENSE", "14": "VBAT_SENSE",
    "15": "RSV_PA0", "16": "NRST", "17": "RSV_PC15", "18": "RSV_PC14",
    "19": "RSV_PC13", "20": "RSV_VBAT_RTC",
    "21": "RSV_PB12", "22": "RSV_PB13", "23": "RSV_PB14", "24": "RSV_PB15",
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    "34": "UART1_TX", "35": "UART1_RX", "36": "I2C_SCL", "37": "I2C_SDA",
    "38": "+5V", "39": "GND", "40": "+3V3",
    "41": "+3V3", "42": "SWDIO", "43": "SWCLK", "44": "GND"},
  nc=("28", "29"),          # PA11/PA12 = USB D-/D+ na module, nie ruszamy
  descr="WeAct BlackPill V3.1, STM32F411CEU6. PA11/PA12 zajete przez USB modulu.")

# ---------------------------------------------------------------- czujniki
C("A2", "SparrowHawk_Modules:Module_LSM6DSO32_Adafruit_4692",
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  descr="Standard SparrowHawk: VBAT, GND, prad, M1-M4, zapas.")
C("J_RX1", "Connector_Generic:Conn_01x04", "RX 1x4 SH", SH4, 330.2, 92.71,
  nets={"1": "+5V", "2": "GND", "3": "UART1_RX", "4": "UART1_TX"},
  descr="Odbiornik na USART1 (PB7 = RX, PB6 = TX).")
C("J_GPS1", "Connector_Generic:Conn_01x04", "GPS 1x4 SH", SH4, 330.2, 118.11,
  nets={"1": "+5V", "2": "GND", "3": "I2C_SCL", "4": "I2C_SDA"},
  descr="GPS/magnetometr na I2C1 (PB8/PB9).")
C("J_SWD1", "Connector_Generic:Conn_01x04", "SWD 1x4", PH(4), 330.2, 143.51,
  nets={"1": "+3V3", "2": "SWDIO", "3": "SWCLK", "4": "GND"},
  descr="SWD wyprowadzone z gniazda 1x4 pod modulem na krawedz plytki.")
C("J_PA3_1", "Connector_Generic:Conn_01x04", "PA3 / zapas ESC", PH(4), 330.2, 166.37,
  nets={"1": "PA3_AUX", "2": "ESC_SPARE", "3": "GND", "4": "+3V3"},
  descr="Zworka PA3 (analog albo USART2_RX) plus zapasowa linia ze zlacza ESC.")
C("J_AUX_A1", "Connector_Generic:Conn_01x08", "Rezerwa rzad A", PH(8), 330.2, 199.39,
  nets={"1": "RSV_PA4", "2": "RSV_PB2", "3": "RSV_PA0", "4": "NRST",
        "5": "RSV_PC15", "6": "RSV_PC14", "7": "RSV_PC13", "8": "RSV_VBAT_RTC"},
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C("J_AUX_B1", "Connector_Generic:Conn_01x07", "Rezerwa rzad B", PH(7), 330.2, 240.03,
  nets={"1": "RSV_PB12", "2": "RSV_PB13", "3": "RSV_PB14", "4": "RSV_PB15",
        "5": "RSV_PA9", "6": "RSV_PA10", "7": "RSV_PB3"},
  descr="Nieuzyte piny rzedu B na goldpiny. PA11/PA12 pominiete - to USB.")

# ---------------------------------------------------------------- mechanika
# Otwory musza byc elementami schematu. Footprinty dodane tylko w mkboard.py
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MX = SX
for i, m in enumerate(("M1", "M2", "M3", "M4")):
    passive(f"R_PD_{m}", "Device:R", "4.7k", R04, MX + i*STEP, SY4, m, "GND",
            descr="Sciagacz - PB4 to JTRST z wewnetrznym podciagnieciem ~40k.")

passive("R_I2C1", "Device:R", "4.7k", R04, MX + 4*STEP, SY4, "+3V3", "I2C_SCL")
passive("R_I2C2", "Device:R", "4.7k", R04, MX + 5*STEP, SY4, "+3V3", "I2C_SDA")
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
